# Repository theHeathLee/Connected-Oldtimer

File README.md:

# Connected-Oldtimer

The aim of this project to modernize my old Volkswagen T2 by adding sensors everywhere and make it part of the internet of things. This project is not vehicle specific and can be implimented in any pre OBD vehicle.

The goal here is first to make remote monitoring possible. Motion sensing for anti theft will be implemented as the vehicle does a lot of sitting. (my bicycle has x4 the ammount of kms per year on it as the bus). Additionaly the ability to remotely view levels (battery charge, fuel level etc..)

Alongside remote monitoring I have implmented an HMI using a 3.5" Display that fits in the dash area originally inteded for the RPM guage. This display shows the instantanious data such as speed, RPM, and Temperature.

A low speed CAN network is set up throughout the vehicle to easily add extra sensors.

Disclaimer: Still in the __developement phase__. V1 hardware has been created and software is still in heavy developement.

### Software used:
- Visual Studio Code w/ [Particle Workbench Extentsion](https://marketplace.visualstudio.com/items?itemName=particle.particle-vscode-pack)🤘
- Particle [Cloud](https://www.particle.io/device-cloud/) 
- [BusMaster](http://rbei-etas.github.io/busmaster/)

### Things implemented:

- 3G Connectivity and vehicle to [cloud](https://www.particle.io/device-cloud/) data transfer   
- Gps velocity and location tracking and display  
- CAN Bus Sensor Data
- Movement Sensor 
- 3D Printed Display mount ([Thingiverse](https://www.thingiverse.com/thing:4713912))

### Parts List:

- [Particle Electron](https://www.particle.io/cellular/)
- [Nextion 3.5" Display](https://www.itead.cc/nextion-nx4832t035.html)
- [Adafruit Ultimage GPS](https://www.adafruit.com/product/746)
- [Adafruit I2C FRAM](https://www.adafruit.com/product/1895)
- [Shock Sensor SW-420](https://components101.com/sensors/sw-420-vibration-sensor-module)
- [CAN Bus Tranceiver Module (TJA1051)](https://www.nxp.com/products/analog/interfaces/in-vehicle-network/can-transceiver-and-controllers/high-speed-can-transceiver:TJA1051)
- [CAN Bus Cable](https://www.conrad.de/de/p/busleitung-unitronic-bus-2-x-2-x-0-22-mm-violett-lapp-2170261-meterware-604030.html)
- PCB From this Repo
- [~~Fuel Flow Meter~~](https://www.conrad.com/p/bt-bio-tech-fch-m-pom-lc-ad-6-mm-low-flow-flowmeter-non-corrosive-liquids-water-diesel-oil-150392?searchTerm=150392&searchType=suggest&searchSuggest=product)

# End Product

# Hardware

[BOM Viewer](https://htmlpreview.github.io/?https://github.com/theHeathLee/Connected-Oldtimer/blob/master/Hardware/Connected-OldtimerHardware/bom/ibom.html)

### Schematic

### PCB

## 3D Printed Bracket

Art Credits:
[Freepik](https://www.flaticon.com/authors/freepik)

## CAN Matrix

| Value       | ID        |DLC   | Byte Pos.|
| ------------- |:-----:|----:|   --:|
| Temp (C)     | 0x100 | 8 |0 |
| RPM     | 0x200 | 8 |0, 1|
| Fuel Level    | 0x300 | 8 |0 |
| Fuel Flow    | 0x400 | 8 |0 |

## Nextion Component Values

| Component  | Value        |
| ------------- |:-----:|
Speed (Kmh) | n0
Odometer (Km) | n1
Trip Counter (Km) | n3
CHT (C) | n2
RPM | va0

# References

## GPS

### NMEA Simulation
[SatGen](https://www.labsat.co.uk/index.php/de/free-gps-nmea-simulator-software) Windows software form LabSat used for playing NMEA files over virtual coms

[NMEAGen](https://nmeagen.org/) browser application for generating custom NMEA files

To create a GPS simulation, first create an NMEA file in NMEAGen. after generating a .nmea file, change the file extension to .txt. The file can now be played in the Serial Output tab of SatGen.

Any USB to TTL coverter can be connected to ports C0 & C1 (Serial5) of the Electron.

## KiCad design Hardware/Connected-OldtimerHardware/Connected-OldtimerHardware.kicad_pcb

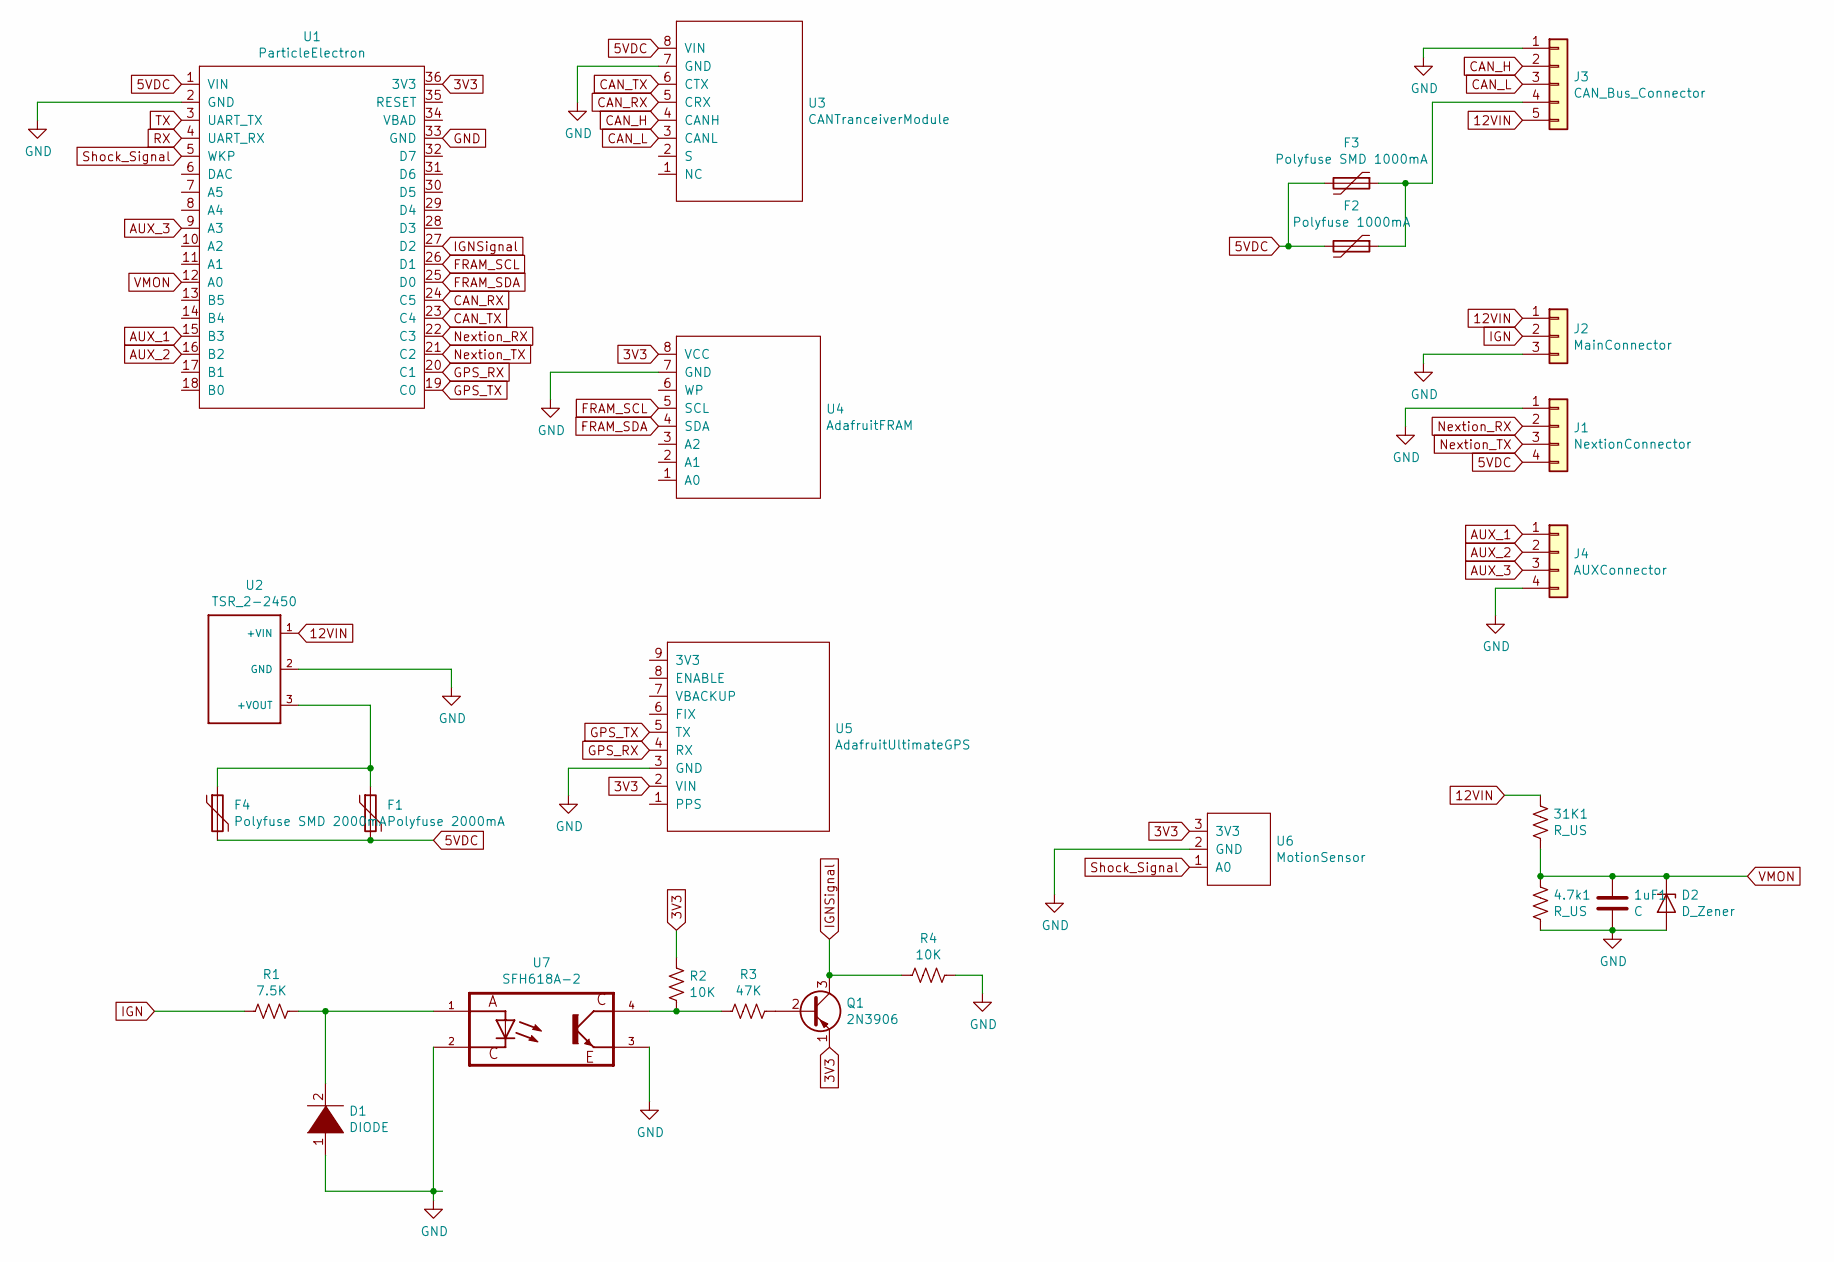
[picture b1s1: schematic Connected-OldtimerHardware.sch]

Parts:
1uF1: C; C_Disc_D8.0mm_W2.5mm_P5.00mm
4.7k1, 31K1: R_US; R_Axial_DIN0207_L6.3mm_D2.5mm_P10.16mm_Horizontal
D1: DIODE; D_A-405_P10.16mm_Horizontal
D2: D_Zener; D_DO-41_SOD81_P7.62mm_Horizontal
F1: Polyfuse 2000mA; Fuse_Littelfuse-LVR200
F2: Polyfuse 1000mA; Fuse_Littelfuse-LVR200
F3: Polyfuse SMD 1000mA; C_1210_3225Metric_Pad1.42x2.65mm_HandSolder
F4: Polyfuse SMD 2000mA; C_1210_3225Metric_Pad1.42x2.65mm_HandSolder
J1: NextionConnector; JST_XH_S04B-XH-A-1_1x04_P2.50mm_Horizontal
J2: MainConnector; JST_XH_S03B-XH-A-1_1x03_P2.50mm_Horizontal
J3: CAN_Bus_Connector; JST_XH_S05B-XH-A-1_1x05_P2.50mm_Horizontal
J4: AUXConnector; JST_XH_S04B-XH-A-1_1x04_P2.50mm_Horizontal
Q1: 2N3906; TO-92_Inline
R1: 7.5K; R_Axial_DIN0207_L6.3mm_D2.5mm_P10.16mm_Horizontal
R2, R4: 10K; R_Axial_DIN0207_L6.3mm_D2.5mm_P10.16mm_Horizontal
R3: 47K; R_Axial_DIN0207_L6.3mm_D2.5mm_P10.16mm_Horizontal
U1: ParticleElectron; electron
U2: TSR_2-2450; heathsTRS_2_2450
U3: CANTranceiverModule; CAN_Tranceiver_Module
U4: AdafruitFRAM; Adafruit_I2C_FRAM
U5: AdafruitUltimateGPS
U6: MotionSensor; ShockSensor
U7: SFH618A-2; DIP-4_W7.62mm_Socket

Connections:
3V3: Q1.1 (E), R2.1, U1.36 (3V3), U4.8 (VCC), U5.2 (VIN), U6.3 (3V3)
5VDC: F1.2, F2.2, F3.2, F4.2, J1.4, U1.1 (VIN), U3.8 (VIN)
12VIN: 31K1.1, J2.1, J3.5, U2.1 (+VIN)
AUX_1: J4.1, U1.15 (B3)
AUX_2: J4.2, U1.16 (B2)
AUX_3: J4.3, U1.9 (A3)
CAN_H: J3.2, U3.4 (CANH)
CAN_L: J3.3, U3.3 (CANL)
CAN_RX: U1.24 (C5), U3.5 (CRX)
CAN_TX: U1.23 (C4), U3.6 (CTX)
FRAM_SCL: U1.26 (D1), U4.5 (SCL)
FRAM_SDA: U1.25 (D0), U4.4 (SDA)
GND: 1uF1.2, 4.7k1.2, D1.1 (K), D2.2 (A), J1.1, J2.3, J3.1, J4.4, R4.1, U1.2 (GND), U1.33 (GND), U2.2 (GND), U3.7 (GND), U4.7 (GND), U5.3 (GND), U6.2 (GND), U7.2 (C), U7.3 (E)
GPS_RX: U1.20 (C1), U5.4 (RX)
GPS_TX: U1.19 (C0), U5.5 (TX)
IGN: J2.2, R1.2
IGNSignal: Q1.3 (C), R4.2, U1.27 (D2)
unnamed: D1.2 (A), R1.1, U7.1 (A)
unnamed: F1.1, F4.1, U2.3 (+VOUT)
unnamed: F2.1, F3.1, J3.4
unnamed: Q1.2 (B), R3.1
unnamed: R2.2, R3.2, U7.4 (CO)
Nextion_RX: J1.2, U1.22 (C3)
Nextion_TX: J1.3, U1.21 (C2)
RX: U1.4 (UART_RX)
Shock_Signal: U1.5 (WKP), U6.1 (A0)
TX: U1.3 (UART_TX)
VMON: 1uF1.1, 4.7k1.1, 31K1.2, D2.1 (K), U1.12 (A0)

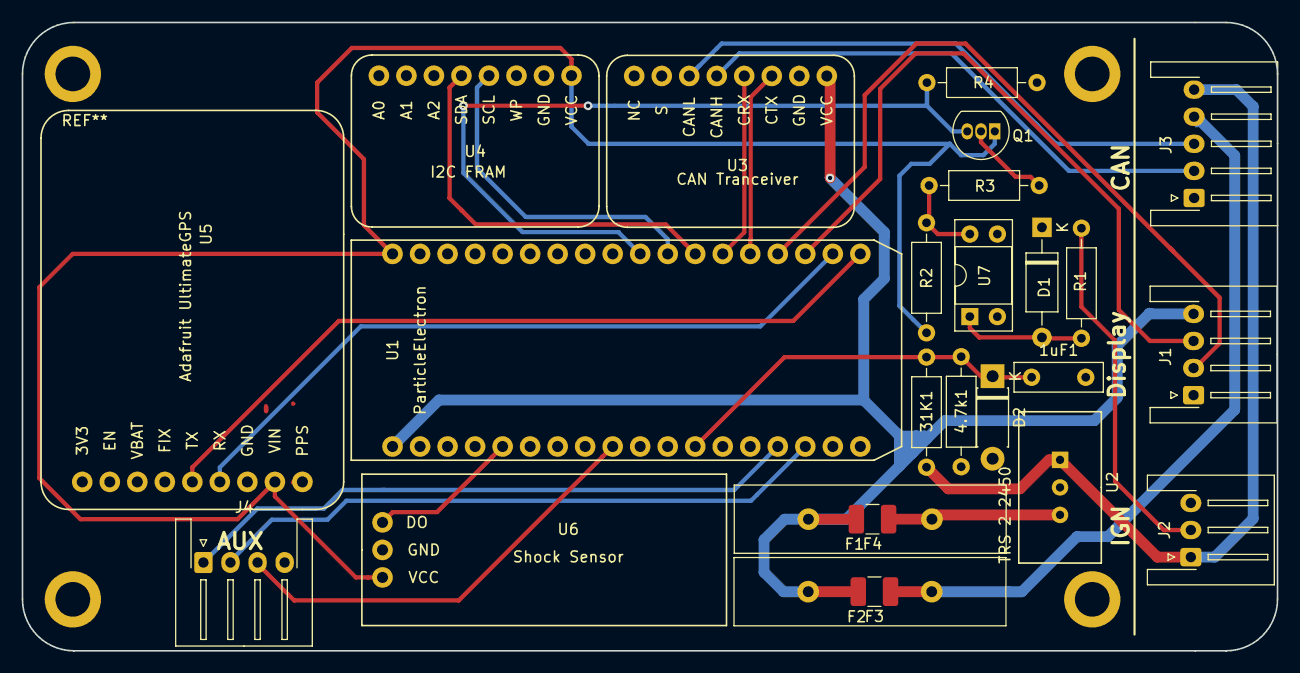
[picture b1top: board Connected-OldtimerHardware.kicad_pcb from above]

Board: 2 copper layers, 115.8 x 58.0 mm, 25 parts (0 on the bottom side), 26 nets.

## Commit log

2019-03-24 Added code
2019-03-26 added tinyGPS++ Library
2019-03-26 activated serial 5
2019-03-27 gps coordinates
2019-03-27 send gps speed to display
2019-03-27 added can bus receive function
2019-04-08 screen updates from gps speed
2019-05-04 fixed GPS Speed read
    changed data type to a double
2019-05-04 fixed speed update
    nextion speed has to be uint8_t
2019-05-04 fixed Speed rounding
2019-05-04 deactivated debug speed
2019-05-06 almost working
2019-05-06 sends dummy data to cloud
2019-05-07 Added gitignore
2019-05-07 removed comment
2019-05-08 changed Baud to 250
2019-05-13 Added Can send function
2019-05-13 Heavily revised readme
2019-05-13 added progress bar
2019-05-13 fixed progress bar
2019-05-13 Added even more progress bars!
2019-05-13 updated GPS Progress
2019-05-13 removed a progress bar
2019-05-13 added todos
2019-05-13 reduced readme in code
2019-05-13 added thingiverse info
2019-05-14 moved status LED into its own function
2019-05-14 Thanos snaps his fingers
2019-05-14 removed delays and added for functions
    converted delays to time differences
2019-05-14 modified readme
2019-05-19 added HMI file
2019-05-20 added banner
2019-05-21 fixed status led timing
2019-05-21 changed can message length
2019-05-21 added display refresh delay
2019-05-28 used struct
2019-07-08 added library
2019-07-08 added empty write to FRAM function
2019-07-08 added a git ignore
2019-07-08 switched libraries
2019-07-08 added MB85RC256V lib files
2019-07-09 I2C Fram Sign of life
2019-07-09 working write/read
2019-07-09 FRAM with two datas
2019-07-09 full functional FRAM storage
2019-07-10 quick fix CAN pins
2019-07-10 attempting to use timers
2019-07-29 removed stress code
2019-08-27 Started Hardware KiCAD Project
2019-08-27 added electron footprint
2019-08-28 Added electron symbol and defined pins
2019-08-28 added modules
2019-09-02 changed can bus to custom module
2019-09-02 changed electron to module
2019-09-02 rest of module conversions
2019-09-02 added 12 to 5 V Switching Regulator
2019-09-02 added opto coupler
2019-09-02 completed Ignition Opto Coupler
2019-09-03 changed GPS to 3.3V Power
2019-09-03 completed footprints
2019-09-03 reordered can module pins
2019-09-03 renamed pinflags to purposes
2019-09-03 added polyfuses
2019-09-03 redid Regulator Footprint
2019-09-04 layout v1
2019-09-04 all connections except ground and 5v
2019-09-04 completed tracks
2019-09-04 minor changes
2019-09-05 changed up connectors
2019-09-05 camper silkscreen
2019-09-05 made dem tracks thick
2019-09-05 switched to horizontal plugs
2019-09-06 Generated Gerbers
2019-09-09 created BOM
2019-09-24 updated Nextion Version
2019-09-24 reverted back !timers
2019-09-24 Removed broke progress bars
2019-10-04 Super Manual Merge!
2019-10-04 moved all serial logs to one function
2019-10-04 added speed prints
2019-10-04 repaired GPS
2019-10-04 speed up read
2019-10-05 TimingFixedwithKaro
2019-10-05 Timings Based on 2 Heartbeats (200mS and 1S)
2019-10-07 distance algorithm implemented
2019-10-07 store last known positions in Fram
2019-10-07 sends Odo value to display
2019-10-07 added odometer val
2019-10-08 tested working TODO: convert delta-cord. to KM
2019-10-09 Great-Circle Distance calculation
2019-10-09 timer reset was missing
2019-10-10 GPS Dev info
2019-10-10 2 pictures
2019-10-10 resize photo
2019-10-11 more print statements
2019-10-11 routine from geodatasource.com
2019-10-14 converted odometer to a double
2019-10-14 working haversine
2019-10-14 ready for test
2019-10-16 Working Display Odometer
2019-10-16 hdop value rather than average filter
2019-10-16 re added fram write
2019-10-16 cleanup
2019-10-18 fixed Km Jumping on startup
2019-10-18 manually added current hmi file
2019-10-21 removed hdop debug to display
2019-10-21 update odo only if speed > 3
2019-10-21 changed to 1
2019-10-28 changed Odo to miles
2020-01-12 added temp readout with color changing bar
2020-01-12 Added new font and completed RPM Addition
2020-03-01 fixed rpm guage
2020-03-01 added photo
2020-03-01 removed smudge from display
2020-03-17 add temp from CAN to display
2020-03-17 re added gps getter
2020-04-12 add can matrix
2020-04-13 add schematic to readme
2020-04-13 fix guage flickering
    icons were too close to each other
2020-04-13 add gitattributes
2020-04-13 add rpm to Nextion Table
2020-04-13 fix RPM CAN read
2020-04-17 add trip counter feature
2020-04-17 add trip counter info
2020-04-17 add Nextion Library
2020-04-20 remove nextion for now
2020-04-20 works
2020-04-21 add battery voltage monitor
2020-04-21 added Display power toggle and shock sense signal
2020-04-23 added code for all hardware power management additions
2020-07-08 add trip val to FRAM getter and setter
2020-12-16 fix format of serial send from hex to string values
2020-12-16 fix FRAM addresses
2020-12-16 fix reset trip function and add line return to nextion
2020-12-16 fix commetn
2020-12-16 fixed FRAM setter and beautify
2020-12-17 add iso-tp and UDS libraries
2020-12-21 try one million
2020-12-24 no more code errors but build complains about missing functions
2020-12-24 moved user c file into main isotp file. Compiles Successfully :)
2020-12-25 working iso-tp messag, but payload is empty
2020-12-26 fix can payload empty
2021-01-02 added iso tp received stuff. Consecutive frames still not working
2021-01-07 Add AemNet data receive
2021-01-07 working code
2021-01-07 Added BusMaster files
2021-01-09 added gif
2021-01-11 flipped orientation
2021-01-11 Added Itead Nextion lib files
2021-01-11 Changed manual serial to use nexSerial
2021-01-11 use pop command instead of manual serial
2021-01-12 fix not returning to home screen
2021-01-12 final touches
2021-01-12 clean up
2021-01-16 downsized photo
2021-02-22 set baud back to 250 and change var names
2021-02-25 fix GPS last fix cloud send
2021-02-25 add clock and temp to HMI
2023-09-27 added signals and display features
2024-02-18 added oil pressure receive and display update, reduced gps rx read rate
2024-02-18 add gps status signal
2024-02-19 tweeked hmi layout
2024-02-27 deep sleep improved to also activate when ignition not active for extended time
2024-02-27 adjust times
2024-03-03 per parametered
2024-03-03 drive test
